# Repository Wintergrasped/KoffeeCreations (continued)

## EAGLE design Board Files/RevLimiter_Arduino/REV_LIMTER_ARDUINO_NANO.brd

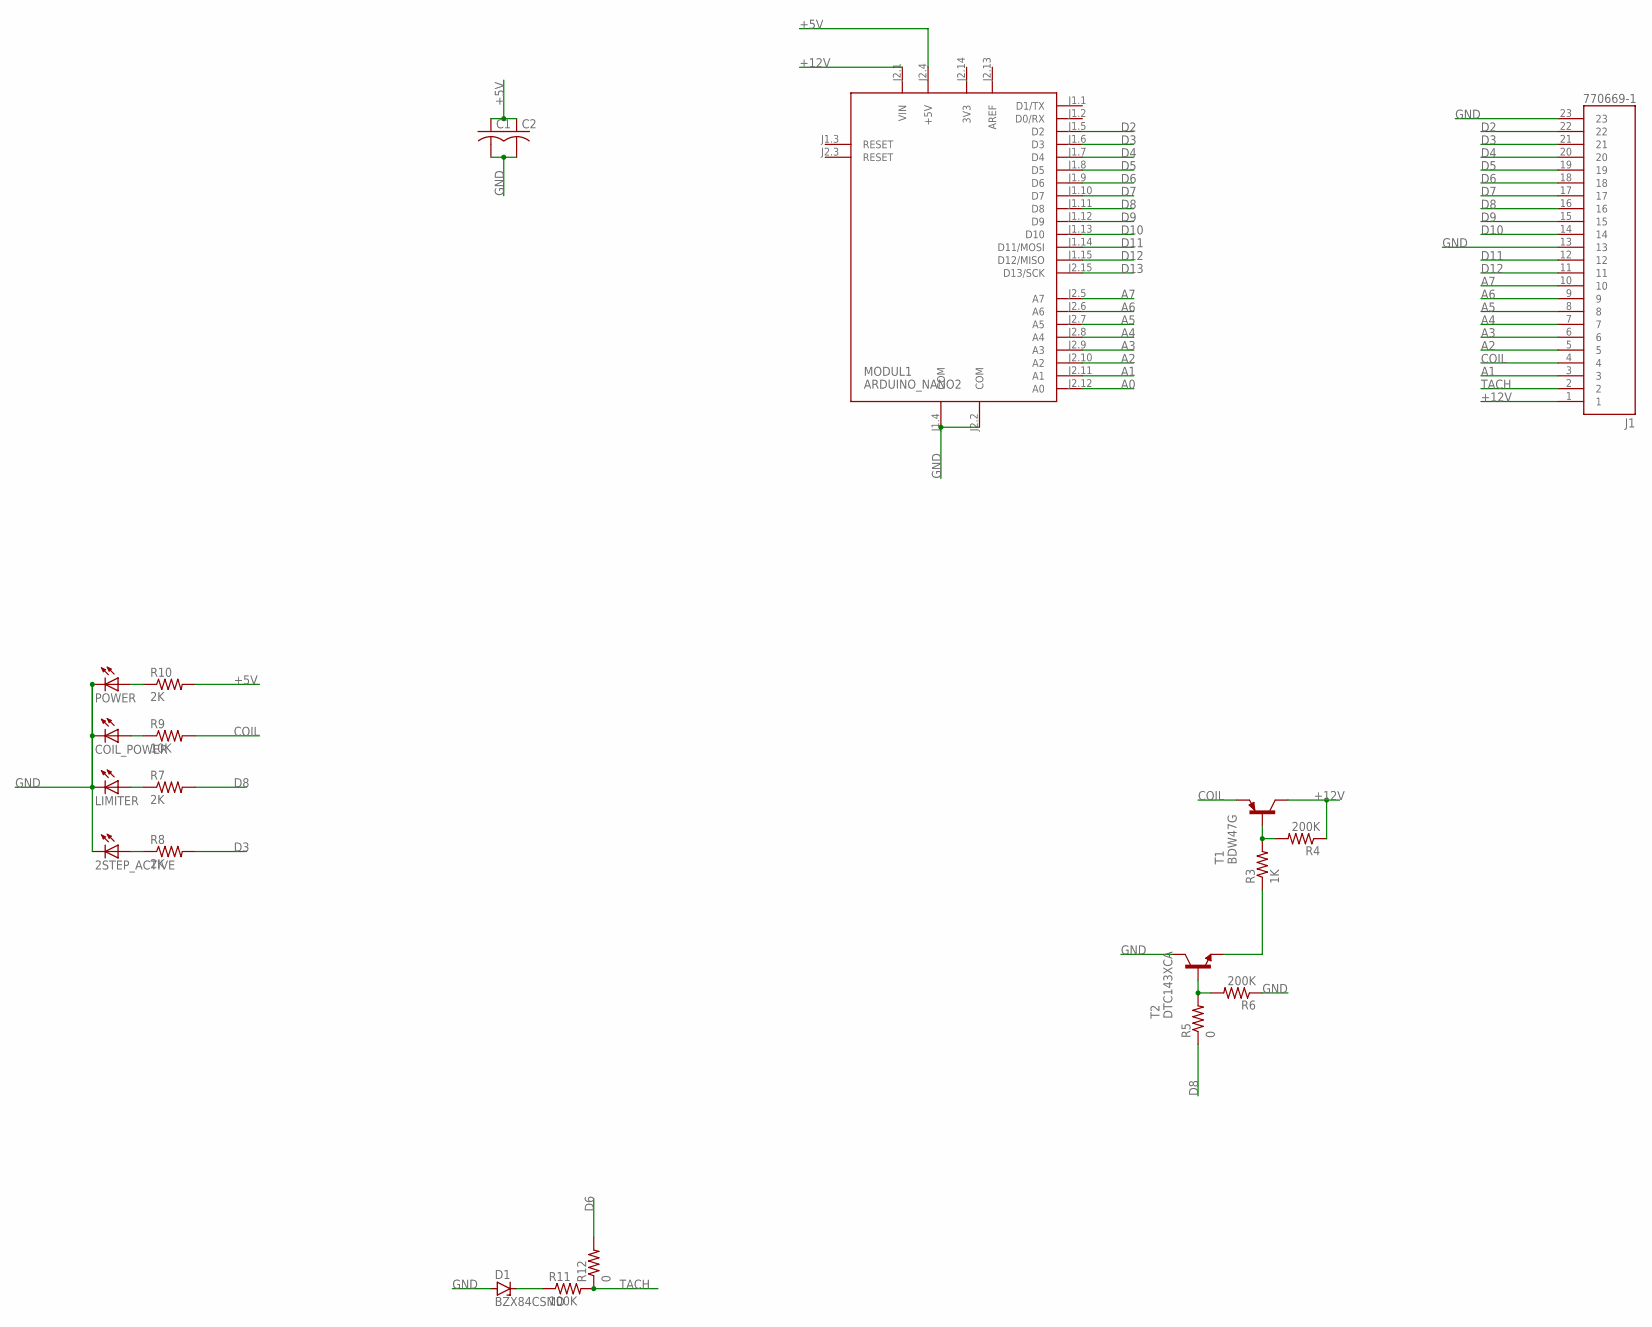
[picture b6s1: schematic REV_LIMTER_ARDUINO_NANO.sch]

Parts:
2STEP_ACTIVE: LED_E; LED_1206
C1, C2: C-USC1206; C1206
COIL_POWER: LED_E; LED_1206
D1: BZX84CSMD; TO236
J1: 770669-1; TE_770669-1
LIMITER: LED_E; LED_1206
MODUL1: ARDUINO_NANO2
POWER: LED_E; LED_1206
R3: 1K; M0805
R4, R6: 200K; M0805
R5: 0; M0805
R7, R8, R10: 2K; R1206
R9: 10K; R1206
R11: 100K; R1206
R12: 0; R0805
T1: BDW47G; TO220V
T2: DTC143XCA; SOT23-BEC

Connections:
3V3: MODUL1.J2.14 (3V3)
+5V: C1.1, C2.1, MODUL1.J2.4 (+5V), R10.2
+12V: J1.1, MODUL1.J2.1 (VIN), R4.1, T1.2 (C)
A0: MODUL1.J2.12 (A0)
A1: J1.3, MODUL1.J2.11 (A1)
A2: J1.5, MODUL1.J2.10 (A2)
A3: J1.6, MODUL1.J2.9 (A3)
A4: J1.7, MODUL1.J2.8 (A4)
A5: J1.8, MODUL1.J2.7 (A5)
A6: J1.9, MODUL1.J2.6 (A6)
A7: J1.10, MODUL1.J2.5 (A7)
AREF: MODUL1.J2.13 (AREF)
COIL: J1.4, R9.2, T1.3 (E)
D2: J1.22, MODUL1.J1.5 (D2)
D3: J1.21, MODUL1.J1.6 (D3), R8.2
D4: J1.20, MODUL1.J1.7 (D4)
D5: J1.19, MODUL1.J1.8 (D5)
D6: J1.18, MODUL1.J1.9 (D6), R12.2
D7: J1.17, MODUL1.J1.10 (D7)
D8: J1.16, MODUL1.J1.11 (D8), R5.1, R7.2
D9: J1.15, MODUL1.J1.12 (D9)
D10: J1.14, MODUL1.J1.13 (D10)
D11: J1.12, MODUL1.J1.14 (D11/MOSI)
D12: J1.11, MODUL1.J1.15 (D12/MISO)
D13: MODUL1.J2.15 (D13/SCK)
GND: 2STEP_ACTIVE.C, C1.2, C2.2, COIL_POWER.C, D1.A, J1.13, J1.23, LIMITER.C, MODUL1.J1.4 (COM), MODUL1.J2.2 (COM), POWER.C, R6.1, T2.C
unnamed: R3.2, R4.2, T1.1 (B)
unnamed: R3.1, T2.E
unnamed: 2STEP_ACTIVE.A, R8.1
unnamed: R5.2, R6.2, T2.B
unnamed: LIMITER.A, R7.1
unnamed: COIL_POWER.A, R9.1
unnamed: POWER.A, R10.1
unnamed: D1.C, R11.1
TACH: J1.2, R11.2, R12.1

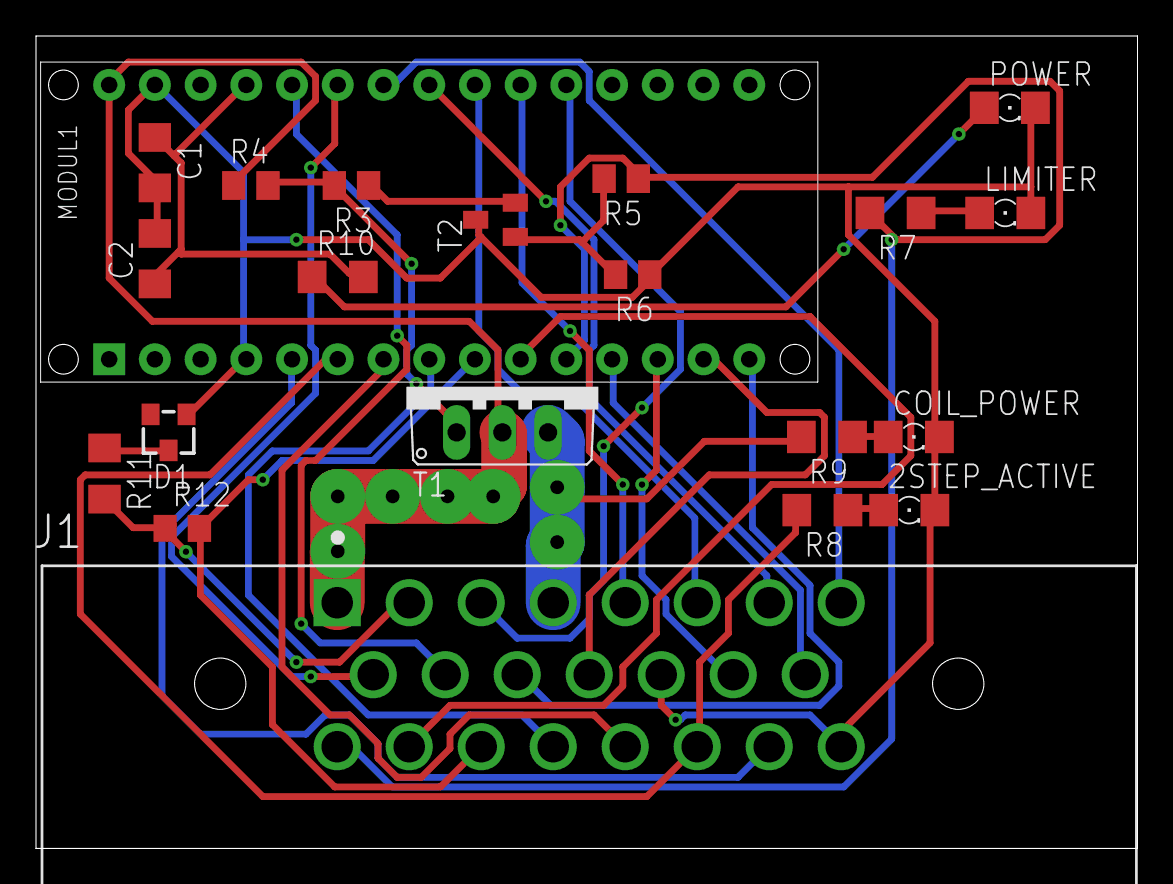
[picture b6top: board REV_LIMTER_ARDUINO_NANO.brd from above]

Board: 2 copper layers, 61.2 x 45.1 mm, 21 parts (0 on the bottom side), 31 nets.

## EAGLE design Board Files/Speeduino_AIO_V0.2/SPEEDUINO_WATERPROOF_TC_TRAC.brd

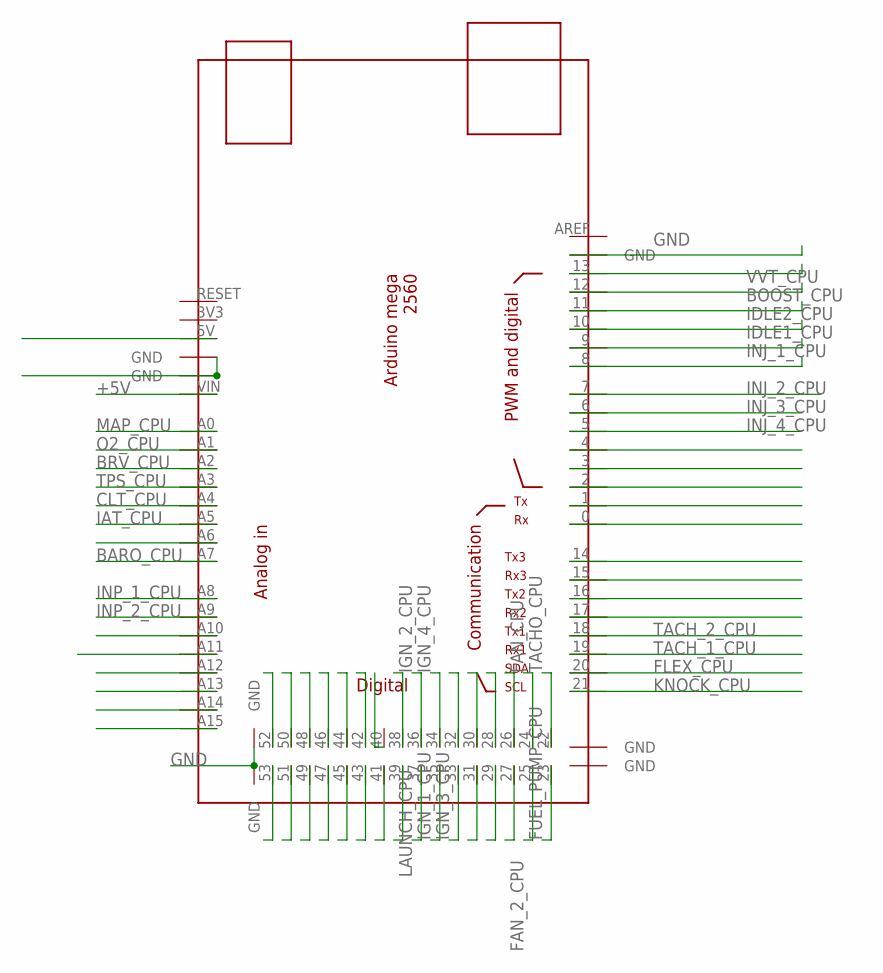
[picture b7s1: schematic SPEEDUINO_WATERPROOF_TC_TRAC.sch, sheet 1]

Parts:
U$1: MEGA_DEVICE; MEGAOUTLINE

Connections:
+5V: U$1.VIN; also elsewhere on the board
BARO_CPU: U$1.A7
BOOST_CPU: U$1.12; also elsewhere on the board
BRV_CPU: U$1.A2; also elsewhere on the board
CLT_CPU: U$1.A4; also elsewhere on the board
FAN_2_CPU: U$1.25; also elsewhere on the board
FAN_CPU: U$1.24; also elsewhere on the board
FLEX_CPU: U$1.20; also elsewhere on the board
FUEL_PUMP_CPU: U$1.23; also elsewhere on the board
GND: U$1.GND@1 (GND), U$1.GND@6 (GND), U$1.GND@7 (GND); also elsewhere on the board
IAT_CPU: U$1.A5; also elsewhere on the board
IDLE1_CPU: U$1.9; also elsewhere on the board
IDLE2_CPU: U$1.10; also elsewhere on the board
IGN_1_CPU: U$1.35; also elsewhere on the board
IGN_2_CPU: U$1.36; also elsewhere on the board
IGN_3_CPU: U$1.33; also elsewhere on the board
IGN_4_CPU: U$1.34; also elsewhere on the board
INJ_1_CPU: U$1.8; also elsewhere on the board
INJ_2_CPU: U$1.7; also elsewhere on the board
INJ_3_CPU: U$1.6; also elsewhere on the board
INJ_4_CPU: U$1.5; also elsewhere on the board
INP_1_CPU: U$1.A8
INP_2_CPU: U$1.A9; also elsewhere on the board
KNOCK_CPU: U$1.21; also elsewhere on the board
LAUNCH_CPU: U$1.37; also elsewhere on the board
MAP_CPU: U$1.A0; also elsewhere on the board
unnamed: U$1.GND@2 (GND), U$1.GND@3 (GND)
O2_CPU: U$1.A1; also elsewhere on the board
TACHO_CPU: U$1.22; also elsewhere on the board
TACH_1_CPU: U$1.19; also elsewhere on the board
TACH_2_CPU: U$1.18; also elsewhere on the board
TPS_CPU: U$1.A3; also elsewhere on the board
VVT_CPU: U$1.13; also elsewhere on the board

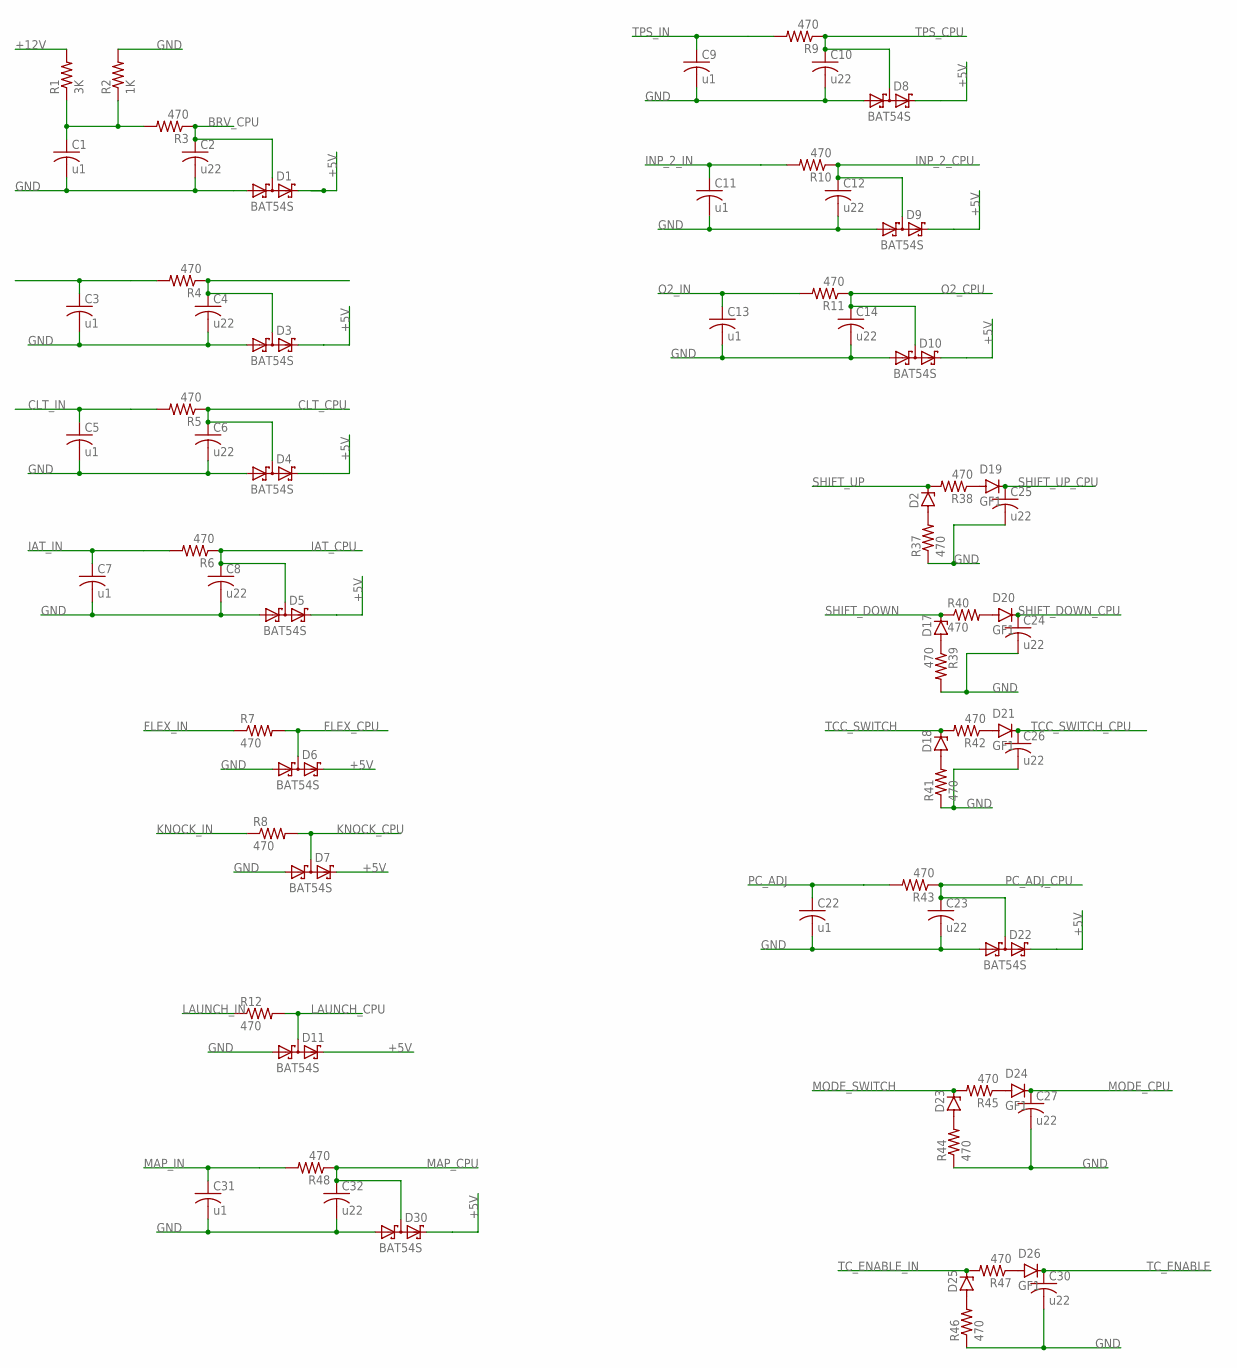
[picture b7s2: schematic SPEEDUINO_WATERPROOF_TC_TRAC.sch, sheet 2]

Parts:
C1, C3, C5, C7, C9, C11, C13, C22, C31: u1; C0805
C2, C4, C6, C8, C10, C12, C14, C23, C24, C25, C26, C27, C30, C32: u22; C0805
D1, D3, D4, D5, D6, D7, D8, D9, D10, D11, D22, D30: BAT54S; SOT23
D2, D17, D18, D23, D25: ZENER-DIODESOT23; SOT23
D19, D20, D21, D24, D26: GF1; SMA-DO214AC
R1: 3K; R0805
R2: 1K; R0805
R3, R4, R5, R6, R9, R10, R11, R37, R38, R39, R40, R41, R42, R43, R44, R45, R46, R47, R48: 470; R0805
R7, R8, R12: 470; R0603

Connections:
+5V: D1.2 (K2), D3.2 (K2), D4.2 (K2), D5.2 (K2), D6.2 (K2), D7.2 (K2), D8.2 (K2), D9.2 (K2), D10.2 (K2), D11.2 (K2), D22.2 (K2), D30.2 (K2); also elsewhere on the board
+12V: R1.2; also elsewhere on the board
BRV_CPU: C2.1, D1.3 (K1A2), R3.1; also elsewhere on the board
CLT_CPU: C6.1, D4.3 (K1A2), R5.1; also elsewhere on the board
CLT_IN: C5.1, R5.2; also elsewhere on the board
FLEX_CPU: D6.3 (K1A2), R7.2; also elsewhere on the board
FLEX_IN: R7.1; also elsewhere on the board
GND: C1.2, C2.2, C3.2, C4.2, C5.2, C6.2, C7.2, C8.2, C9.2, C10.2, C11.2, C12.2, C13.2, C14.2, C22.2, C23.2, C24.2, C25.2, C26.2, C27.2, C30.2, C31.2, C32.2, D1.1 (A1), D3.1 (A1), D4.1 (A1), D5.1 (A1), D6.1 (A1), D7.1 (A1), D8.1 (A1), D9.1 (A1), D10.1 (A1), D11.1 (A1), D22.1 (A1), D30.1 (A1), R2.2, R37.1, R39.2, R41.1, R44.1, R46.1; also elsewhere on the board
IAT_CPU: C8.1, D5.3 (K1A2), R6.1; also elsewhere on the board
IAT_IN: C7.1, R6.2; also elsewhere on the board
INP_2_CPU: C12.1, D9.3 (K1A2), R10.1; also elsewhere on the board
INP_2_IN: C11.1, R10.2
KNOCK_CPU: D7.3 (K1A2), R8.2; also elsewhere on the board
KNOCK_IN: R8.1; also elsewhere on the board
LAUNCH_CPU: D11.3 (K1A2), R12.2; also elsewhere on the board
LAUNCH_IN: R12.1; also elsewhere on the board
MAP_CPU: C32.1, D30.3 (K1A2), R48.1; also elsewhere on the board
MAP_IN: C31.1, R48.2
MODE_CPU: C27.1, D24.K (C); also elsewhere on the board
MODE_SWITCH: D23.3 (C), R45.2; also elsewhere on the board
unnamed: C1.1, R1.1, R2.1, R3.2
unnamed: C3.1, R4.2
unnamed: C4.1, D3.3 (K1A2), R4.1
unnamed: D19.A, R38.1
unnamed: D2.1 (A), R37.2
unnamed: D17.1 (A), R39.1
unnamed: D23.1 (A), R44.2
unnamed: D25.1 (A), R46.2
unnamed: D20.A, R40.2
unnamed: D24.A, R45.1
unnamed: D18.1 (A), R41.2
unnamed: D26.A, R47.1
unnamed: D21.A, R42.1
O2_CPU: C14.1, D10.3 (K1A2), R11.1; also elsewhere on the board
O2_IN: C13.1, R11.2; also elsewhere on the board
PC_ADJ: C22.1, R43.2; also elsewhere on the board
PC_ADJ_CPU: C23.1, D22.3 (K1A2), R43.1; also elsewhere on the board
SHIFT_DOWN: D17.3 (C), R40.1; also elsewhere on the board
SHIFT_DOWN_CPU: C24.1, D20.K (C); also elsewhere on the board
SHIFT_UP: D2.3 (C), R38.2; also elsewhere on the board
SHIFT_UP_CPU: C25.1, D19.K (C); also elsewhere on the board
TCC_SWITCH: D18.3 (C), R42.2; also elsewhere on the board
TCC_SWITCH_CPU: C26.1, D21.K (C); also elsewhere on the board
TC_ENABLE: C30.1, D26.K (C); also elsewhere on the board
TC_ENABLE_IN: D25.3 (C), R47.2; also elsewhere on the board
TPS_CPU: C10.1, D8.3 (K1A2), R9.1; also elsewhere on the board
TPS_IN: C9.1, R9.2; also elsewhere on the board

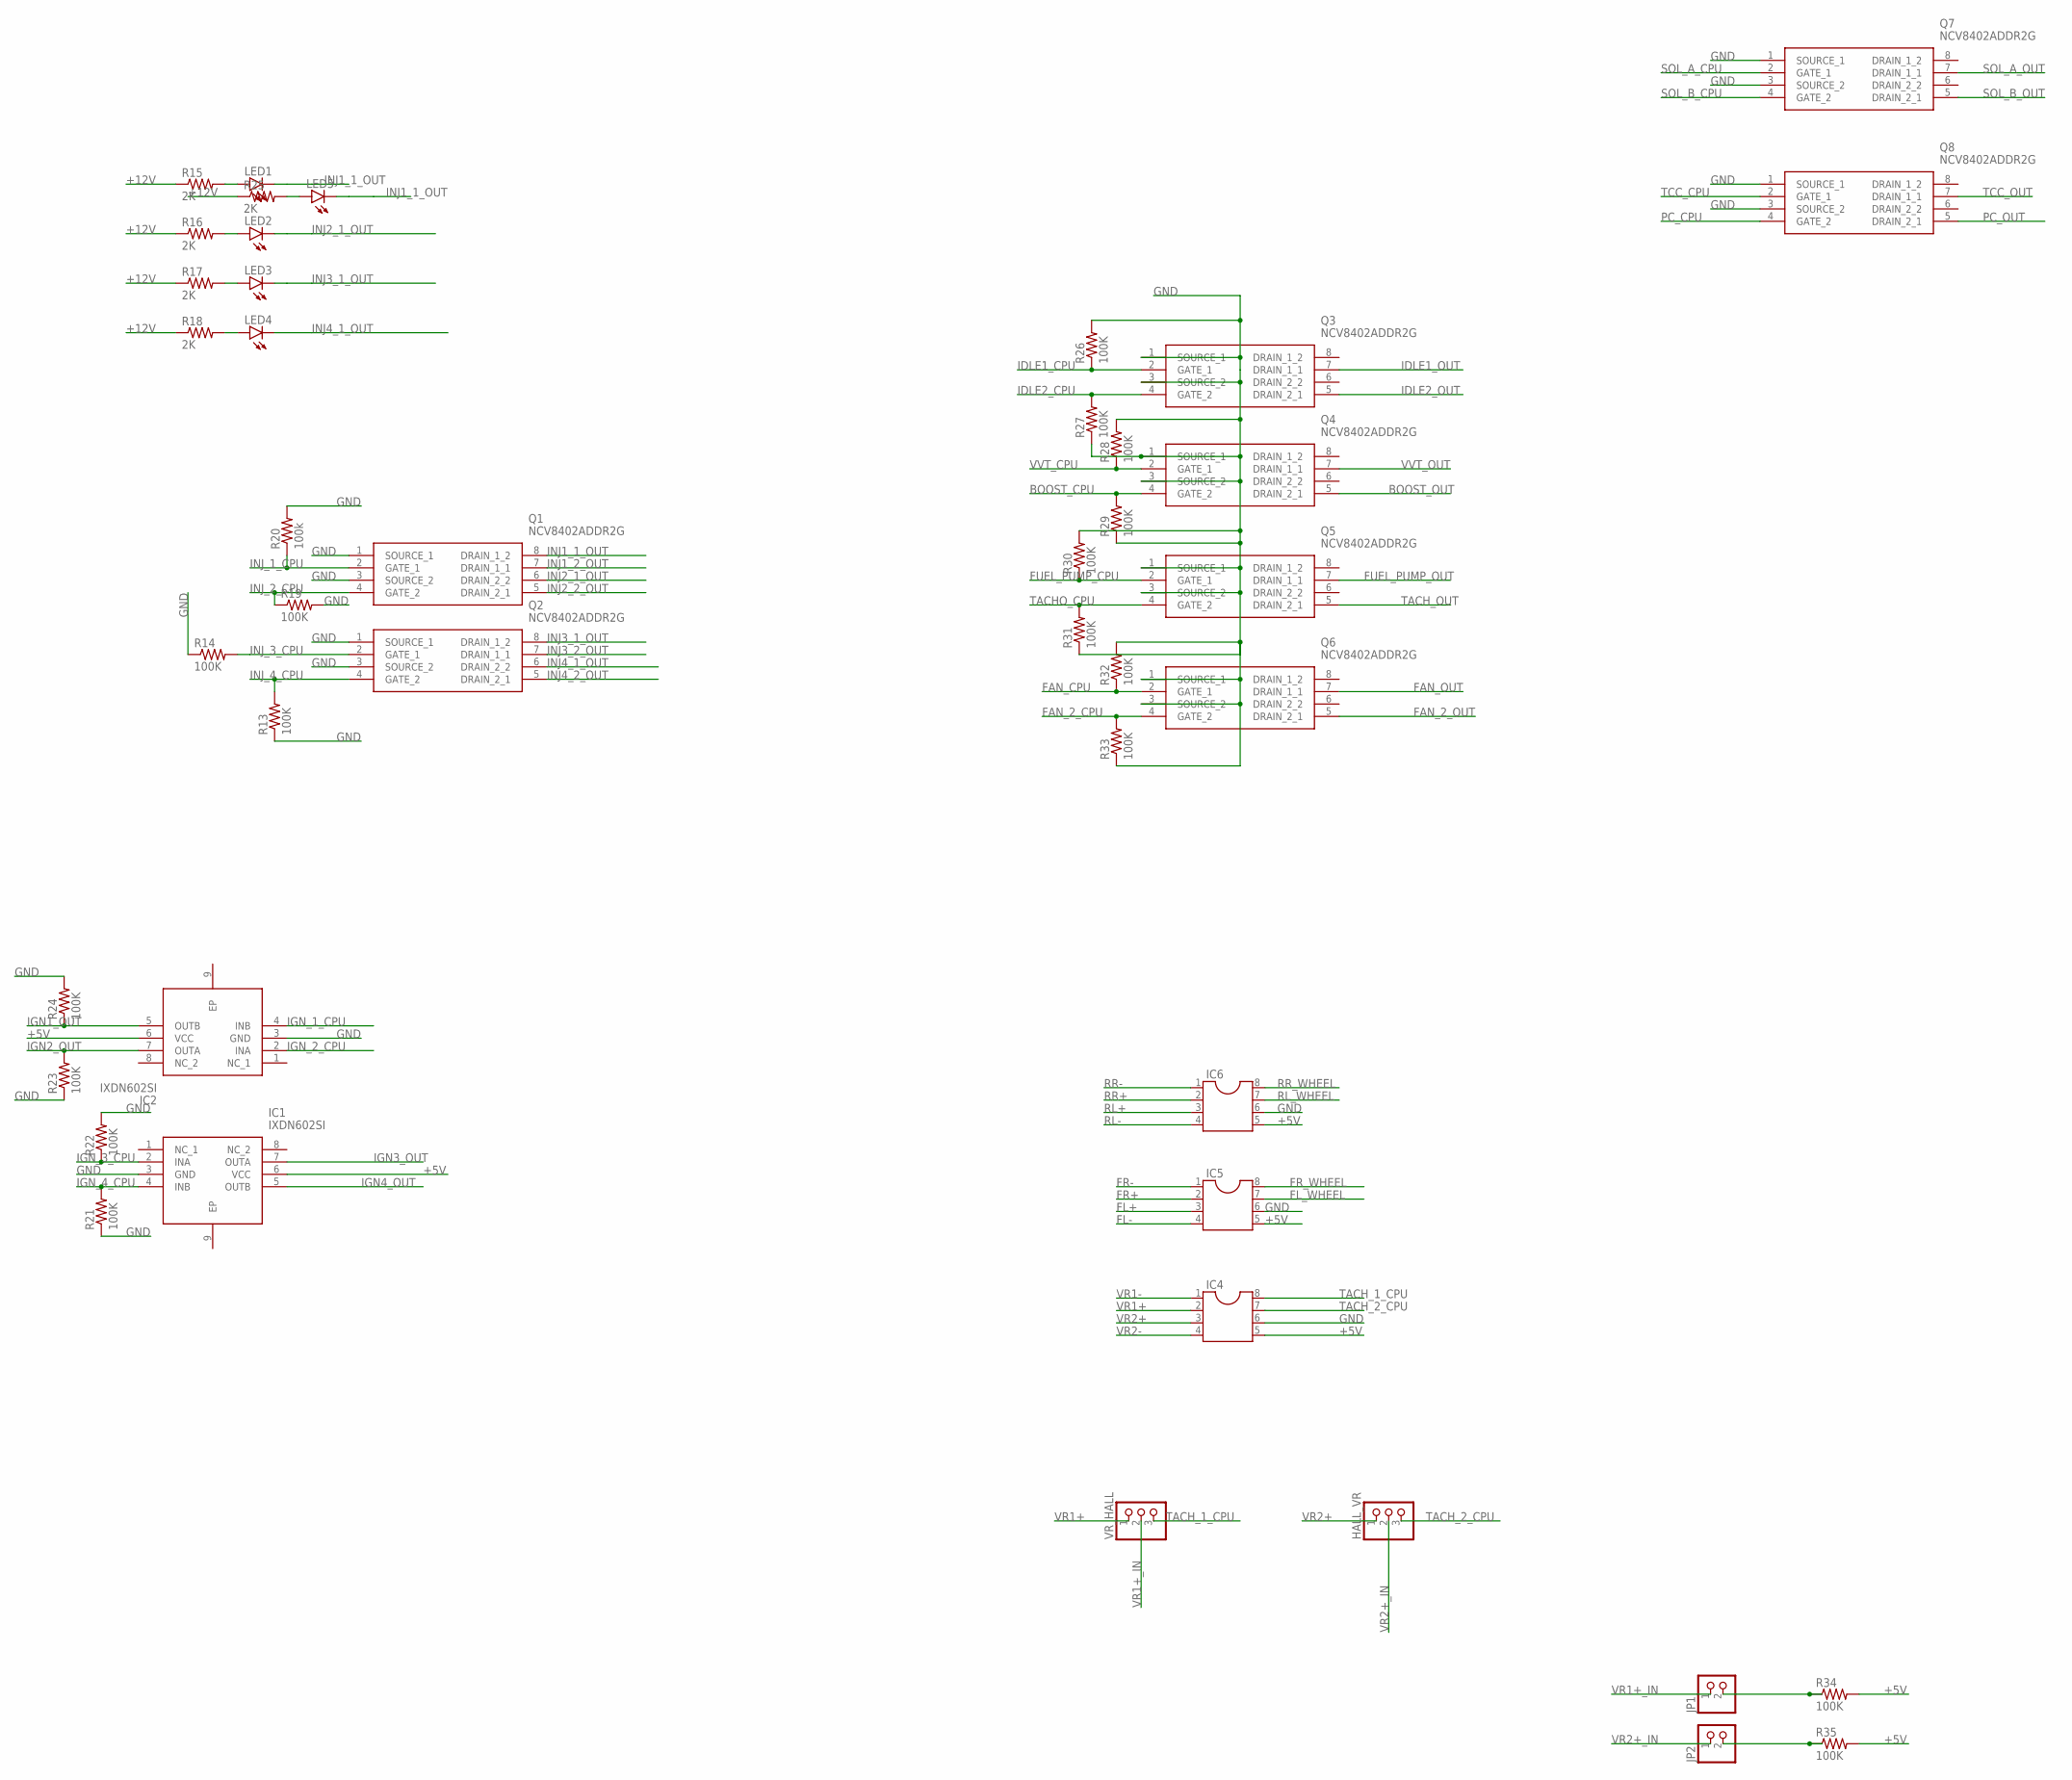
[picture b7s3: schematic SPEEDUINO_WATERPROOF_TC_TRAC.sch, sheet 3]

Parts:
HALL_VR: PINHD-1X3; 1X03
IC1, IC2: IXDN602SI; SOP140P599X142-9N
IC4, IC5, IC6: DIL8; DIL08
JP1, JP2: PINHD-1X2; 1X02
LED1, LED2, LED3, LED4, LED5: LEDCHIP-LED0805; CHIP-LED0805
Q1, Q2, Q3, Q4, Q5, Q6, Q7, Q8: NCV8402ADDR2G; SOIC127P600X175-8N
R13, R14, R19, R21, R22, R23, R24, R26, R27, R28, R29, R30, R31, R32, R33, R34, R35: 100K; R0805
R15, R16, R17, R18, R25: 2K; R0805
R20: 100k; R0805
VR_HALL: PINHD-1X3; 1X03

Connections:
+5V: IC1.6 (VCC), IC2.6 (VCC), IC4.5, IC5.5, IC6.5, R34.2, R35.2; also elsewhere on the board
+12V: R15.1, R16.1, R17.1, R18.1, R25.1; also elsewhere on the board
BOOST_CPU: Q4.4 (GATE_2), R29.2; also elsewhere on the board
BOOST_OUT: Q4.5 (DRAIN_2_1); also elsewhere on the board
FAN_2_CPU: Q6.4 (GATE_2), R33.2; also elsewhere on the board
FAN_2_OUT: Q6.5 (DRAIN_2_1)
FAN_CPU: Q6.2 (GATE_1), R32.1; also elsewhere on the board
FAN_OUT: Q6.7 (DRAIN_1_1); also elsewhere on the board
FL+: IC5.3; also elsewhere on the board
FL-: IC5.4; also elsewhere on the board
FL_WHEEL: IC5.7; also elsewhere on the board
FR+: IC5.2; also elsewhere on the board
FR-: IC5.1; also elsewhere on the board
FR_WHEEL: IC5.8; also elsewhere on the board
FUEL_PUMP_CPU: Q5.2 (GATE_1), R30.1; also elsewhere on the board
FUEL_PUMP_OUT: Q5.7 (DRAIN_1_1); also elsewhere on the board
GND: IC1.3 (GND), IC2.3 (GND), IC4.6, IC5.6, IC6.6, Q1.1 (SOURCE_1), Q1.3 (SOURCE_2), Q2.1 (SOURCE_1), Q2.3 (SOURCE_2), Q3.1 (SOURCE_1), Q3.3 (SOURCE_2), Q4.1 (SOURCE_1), Q4.3 (SOURCE_2), Q5.1 (SOURCE_1), Q5.3 (SOURCE_2), Q6.1 (SOURCE_1), Q6.3 (SOURCE_2), Q7.1 (SOURCE_1), Q7.3 (SOURCE_2), Q8.1 (SOURCE_1), Q8.3 (SOURCE_2), R13.1, R14.1, R19.2, R20.2, R21.1, R22.2, R23.1, R24.2, R26.2, R27.1, R28.2, R29.1, R30.2, R31.1, R32.2, R33.1; also elsewhere on the board
IDLE1_CPU: Q3.2 (GATE_1), R26.1; also elsewhere on the board
IDLE1_OUT: Q3.7 (DRAIN_1_1); also elsewhere on the board
IDLE2_CPU: Q3.4 (GATE_2), R27.2; also elsewhere on the board
IDLE2_OUT: Q3.5 (DRAIN_2_1); also elsewhere on the board
IGN1_OUT: IC2.5 (OUTB), R24.1; also elsewhere on the board
IGN2_OUT: IC2.7 (OUTA), R23.2; also elsewhere on the board
IGN3_OUT: IC1.7 (OUTA); also elsewhere on the board
IGN4_OUT: IC1.5 (OUTB); also elsewhere on the board
IGN_1_CPU: IC2.4 (INB); also elsewhere on the board
IGN_2_CPU: IC2.2 (INA); also elsewhere on the board
IGN_3_CPU: IC1.2 (INA), R22.1; also elsewhere on the board
IGN_4_CPU: IC1.4 (INB), R21.2; also elsewhere on the board
INJ1_1_OUT: LED1.C, LED5.C, Q1.8 (DRAIN_1_2); also elsewhere on the board
INJ1_2_OUT: Q1.7 (DRAIN_1_1); also elsewhere on the board
INJ2_1_OUT: LED2.C, Q1.6 (DRAIN_2_2); also elsewhere on the board
INJ2_2_OUT: Q1.5 (DRAIN_2_1); also elsewhere on the board
INJ3_1_OUT: LED3.C, Q2.8 (DRAIN_1_2); also elsewhere on the board
INJ3_2_OUT: Q2.7 (DRAIN_1_1); also elsewhere on the board
INJ4_1_OUT: LED4.C, Q2.6 (DRAIN_2_2); also elsewhere on the board
INJ4_2_OUT: Q2.5 (DRAIN_2_1); also elsewhere on the board
INJ_1_CPU: Q1.2 (GATE_1), R20.1; also elsewhere on the board
INJ_2_CPU: Q1.4 (GATE_2), R19.1; also elsewhere on the board
INJ_3_CPU: Q2.2 (GATE_1), R14.2; also elsewhere on the board
INJ_4_CPU: Q2.4 (GATE_2), R13.2; also elsewhere on the board
unnamed: LED2.A, R16.2
unnamed: LED1.A, R15.2
unnamed: LED3.A, R17.2
unnamed: LED4.A, R18.2
unnamed: LED5.A, R25.2
unnamed: JP2.2, R35.1
unnamed: JP1.2, R34.1
PC_CPU: Q8.4 (GATE_2); also elsewhere on the board
PC_OUT: Q8.5 (DRAIN_2_1); also elsewhere on the board
RL+: IC6.3; also elsewhere on the board
RL-: IC6.4; also elsewhere on the board
RL_WHEEL: IC6.7; also elsewhere on the board
RR+: IC6.2; also elsewhere on the board
RR-: IC6.1; also elsewhere on the board
RR_WHEEL: IC6.8; also elsewhere on the board
SOL_A_CPU: Q7.2 (GATE_1); also elsewhere on the board
SOL_A_OUT: Q7.7 (DRAIN_1_1); also elsewhere on the board
SOL_B_CPU: Q7.4 (GATE_2); also elsewhere on the board
SOL_B_OUT: Q7.5 (DRAIN_2_1); also elsewhere on the board
TACHO_CPU: Q5.4 (GATE_2), R31.2; also elsewhere on the board
TACH_1_CPU: IC4.8, VR_HALL.3; also elsewhere on the board
TACH_2_CPU: HALL_VR.3, IC4.7; also elsewhere on the board
TACH_OUT: Q5.5 (DRAIN_2_1); also elsewhere on the board
TCC_CPU: Q8.2 (GATE_1); also elsewhere on the board
TCC_OUT: Q8.7 (DRAIN_1_1); also elsewhere on the board
VR1+: IC4.2, VR_HALL.1
VR1+_IN: JP1.1, VR_HALL.2; also elsewhere on the board
VR1-: IC4.1; also elsewhere on the board
VR2+: HALL_VR.1, IC4.3
VR2+_IN: HALL_VR.2, JP2.1; also elsewhere on the board
VR2-: IC4.4; also elsewhere on the board
VVT_CPU: Q4.2 (GATE_1), R28.1; also elsewhere on the board
VVT_OUT: Q4.7 (DRAIN_1_1); also elsewhere on the board

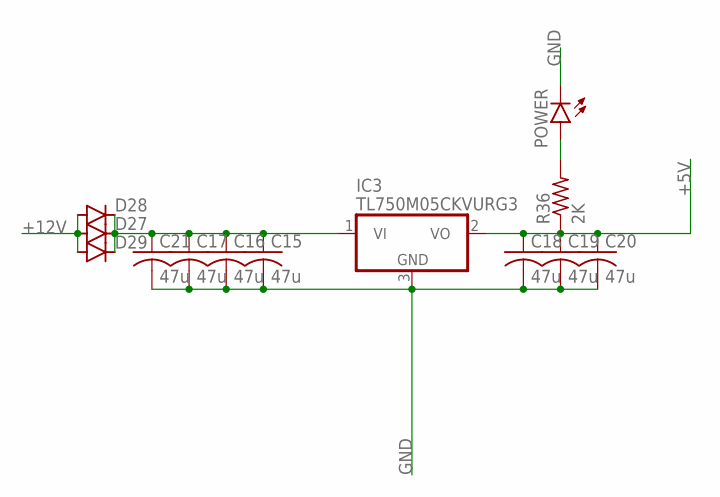
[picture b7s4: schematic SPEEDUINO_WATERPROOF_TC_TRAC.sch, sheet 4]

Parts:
C15, C16, C17, C18, C19, C20, C21: 47u; C0805
D27, D28, D29: DIODE-SOD123; SOD123
IC3: TL750M05CKVURG3; TO252
POWER: LEDCHIP-LED0805; CHIP-LED0805
R36: 2K; R0805

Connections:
+5V: C18.1, C19.1, C20.1, IC3.2 (VO), R36.1; also elsewhere on the board
+12V: D27.A, D28.A, D29.A; also elsewhere on the board
GND: C15.2, C16.2, C17.2, C18.2, C19.2, C20.2, C21.2, IC3.3 (GND), POWER.C; also elsewhere on the board
unnamed: C15.1, C16.1, C17.1, C21.1, D27.C, D28.C, D29.C, IC3.1 (VI)
unnamed: POWER.A, R36.2

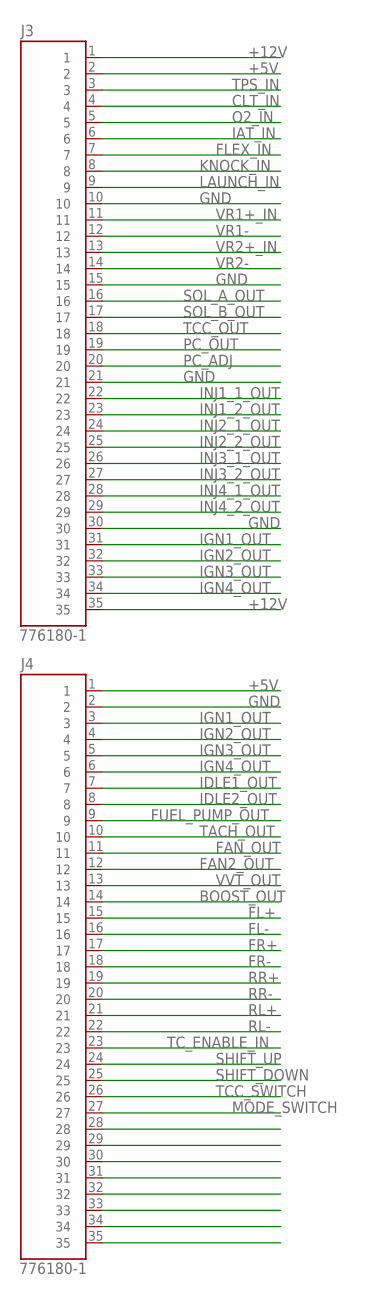
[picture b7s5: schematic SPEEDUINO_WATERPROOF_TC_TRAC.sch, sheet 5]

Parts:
J3, J4: 776180-1; TE_776180-1

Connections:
+5V: J3.2, J4.1; also elsewhere on the board
+12V: J3.1, J3.35; also elsewhere on the board
BOOST_OUT: J4.14; also elsewhere on the board
CLT_IN: J3.4; also elsewhere on the board
FAN2_OUT: J4.12
FAN_OUT: J4.11; also elsewhere on the board
FL+: J4.15; also elsewhere on the board
FL-: J4.16; also elsewhere on the board
FLEX_IN: J3.7; also elsewhere on the board
FR+: J4.17; also elsewhere on the board
FR-: J4.18; also elsewhere on the board
FUEL_PUMP_OUT: J4.9; also elsewhere on the board
GND: J3.10, J3.15, J3.21, J3.30, J4.2; also elsewhere on the board
IAT_IN: J3.6; also elsewhere on the board
IDLE1_OUT: J4.7; also elsewhere on the board
IDLE2_OUT: J4.8; also elsewhere on the board
IGN1_OUT: J3.31, J4.3; also elsewhere on the board
IGN2_OUT: J3.32, J4.4; also elsewhere on the board
IGN3_OUT: J3.33, J4.5; also elsewhere on the board
IGN4_OUT: J3.34, J4.6; also elsewhere on the board
INJ1_1_OUT: J3.22; also elsewhere on the board
INJ1_2_OUT: J3.23; also elsewhere on the board
INJ2_1_OUT: J3.24; also elsewhere on the board
INJ2_2_OUT: J3.25; also elsewhere on the board
INJ3_1_OUT: J3.26; also elsewhere on the board
INJ3_2_OUT: J3.27; also elsewhere on the board
INJ4_1_OUT: J3.28; also elsewhere on the board
INJ4_2_OUT: J3.29; also elsewhere on the board
KNOCK_IN: J3.8; also elsewhere on the board
LAUNCH_IN: J3.9; also elsewhere on the board
MODE_SWITCH: J4.27; also elsewhere on the board
O2_IN: J3.5; also elsewhere on the board
PC_ADJ: J3.20; also elsewhere on the board
PC_OUT: J3.19; also elsewhere on the board
RL+: J4.21; also elsewhere on the board
RL-: J4.22; also elsewhere on the board
RR+: J4.19; also elsewhere on the board
RR-: J4.20; also elsewhere on the board
SHIFT_DOWN: J4.25; also elsewhere on the board
SHIFT_UP: J4.24; also elsewhere on the board
SOL_A_OUT: J3.16; also elsewhere on the board
SOL_B_OUT: J3.17; also elsewhere on the board
TACH_OUT: J4.10; also elsewhere on the board
TCC_OUT: J3.18; also elsewhere on the board
TCC_SWITCH: J4.26; also elsewhere on the board
TC_ENABLE_IN: J4.23; also elsewhere on the board
TPS_IN: J3.3; also elsewhere on the board
VR1+_IN: J3.11; also elsewhere on the board
VR1-: J3.12; also elsewhere on the board
VR2+_IN: J3.13; also elsewhere on the board
VR2-: J3.14; also elsewhere on the board
VVT_OUT: J4.13; also elsewhere on the board

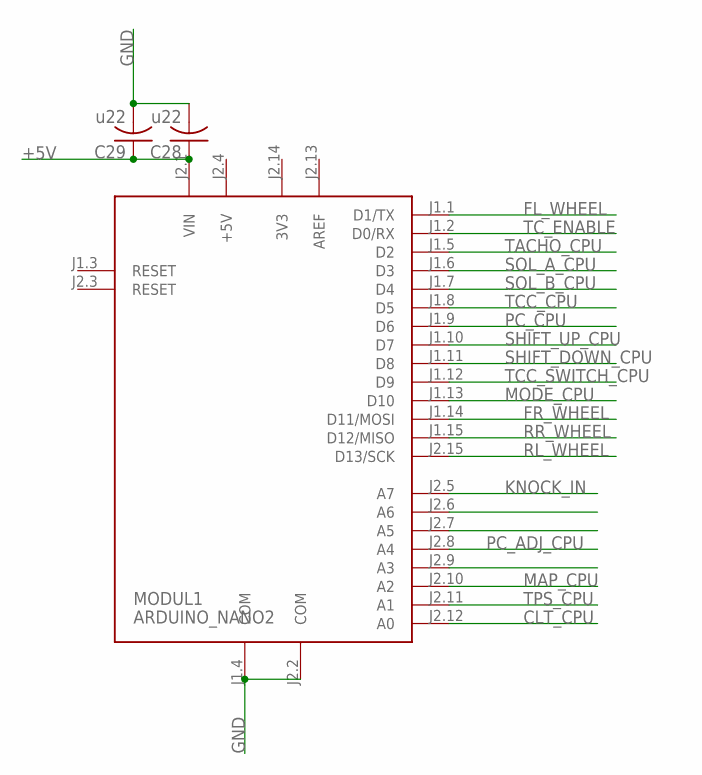
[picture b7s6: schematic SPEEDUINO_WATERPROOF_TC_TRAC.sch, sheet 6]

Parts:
C28, C29: u22; C0805
MODUL1: ARDUINO_NANO2

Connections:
3V3: MODUL1.J2.14 (3V3)
+5V: C28.1, C29.1, MODUL1.J2.1 (VIN), MODUL1.J2.4 (+5V); also elsewhere on the board
AREF: MODUL1.J2.13 (AREF)
CLT_CPU: MODUL1.J2.12 (A0); also elsewhere on the board
FL_WHEEL: MODUL1.J1.1 (D1/TX); also elsewhere on the board
FR_WHEEL: MODUL1.J1.14 (D11/MOSI); also elsewhere on the board
GND: C28.2, C29.2, MODUL1.J1.4 (COM), MODUL1.J2.2 (COM); also elsewhere on the board
KNOCK_IN: MODUL1.J2.5 (A7); also elsewhere on the board
MAP_CPU: MODUL1.J2.10 (A2); also elsewhere on the board
MODE_CPU: MODUL1.J1.13 (D10); also elsewhere on the board
PC_ADJ_CPU: MODUL1.J2.8 (A4); also elsewhere on the board
PC_CPU: MODUL1.J1.9 (D6); also elsewhere on the board
RL_WHEEL: MODUL1.J2.15 (D13/SCK); also elsewhere on the board
RR_WHEEL: MODUL1.J1.15 (D12/MISO); also elsewhere on the board
SHIFT_DOWN_CPU: MODUL1.J1.11 (D8); also elsewhere on the board
SHIFT_UP_CPU: MODUL1.J1.10 (D7); also elsewhere on the board
SOL_A_CPU: MODUL1.J1.6 (D3); also elsewhere on the board
SOL_B_CPU: MODUL1.J1.7 (D4); also elsewhere on the board
TACHO_CPU: MODUL1.J1.5 (D2), MODUL1.J2.9 (A3); also elsewhere on the board
TCC_CPU: MODUL1.J1.8 (D5); also elsewhere on the board
TCC_SWITCH_CPU: MODUL1.J1.12 (D9); also elsewhere on the board
TC_ENABLE: MODUL1.J1.2 (D0/RX); also elsewhere on the board
TPS_CPU: MODUL1.J2.11 (A1); also elsewhere on the board
